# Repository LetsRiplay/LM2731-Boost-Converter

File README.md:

# LM2731-Boost-Converter
Boost converter using a 5V USB-C adapter

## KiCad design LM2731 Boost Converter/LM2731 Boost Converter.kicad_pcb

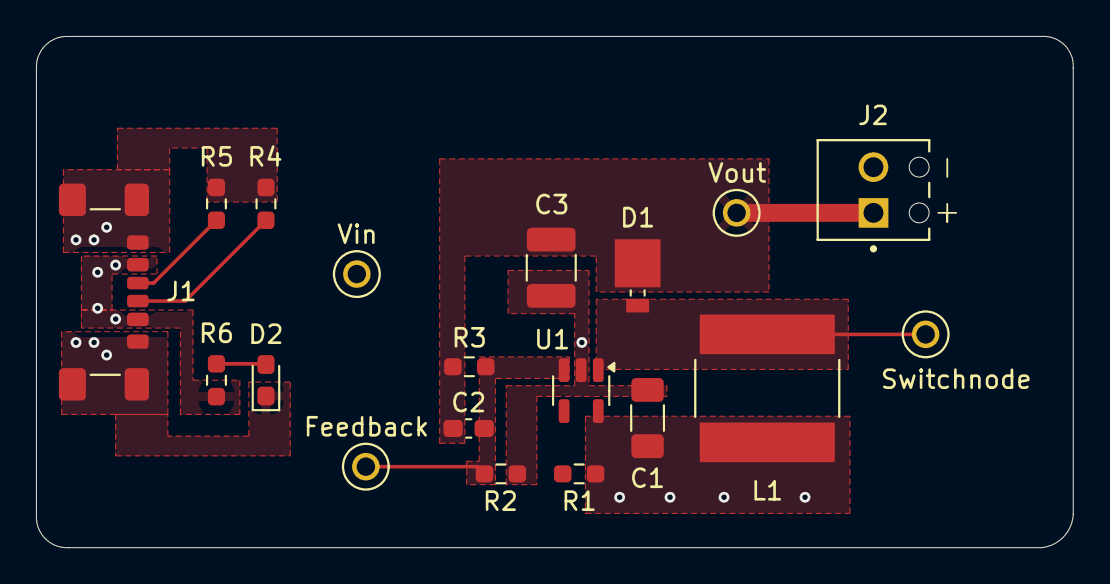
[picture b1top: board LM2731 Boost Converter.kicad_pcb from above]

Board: 4 copper layers, 57.6 x 28.4 mm, 19 parts (0 on the bottom side), 9 nets.

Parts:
C1: 2.2uF; C_1206_3216Metric_Pad1.33x1.80mm_HandSolder
C2: 240pF; C_0603_1608Metric_Pad1.08x0.95mm_HandSolder
C3: 4.7uF; C_1210_3225Metric_Pad1.33x2.70mm_HandSolder
D1: D_Schottky; D_Powermite_AK
D2: LED; LED_0603_1608Metric_Pad1.05x0.95mm_HandSolder
Feedback: TestPoint; KEYSTONE_5000
J1: USB_C_Receptacle_PowerOnly_6P; USB_C_Receptacle_GCT_USB4135-GF-A_6P_TopMnt_Horizontal
J2: Screw_Terminal_01x02; PHOENIX_1725656
L1: 43uH; IND_ASPI-8040S-430M-T
R1: 47k; R_0603_1608Metric_Pad0.98x0.95mm_HandSolder
R2: 13.3k; R_0603_1608Metric_Pad0.98x0.95mm_HandSolder
R3: 117k; R_0603_1608Metric_Pad0.98x0.95mm_HandSolder
R4, R5: 5.1k; R_0603_1608Metric_Pad0.98x0.95mm_HandSolder
R6: 70; R_0603_1608Metric_Pad0.98x0.95mm_HandSolder
Switchnode: TestPoint; KEYSTONE_5000
U1: LM2731YMF; SOT-23-5
Vin: Vin; KEYSTONE_5000
Vout: TestPoint; KEYSTONE_5000

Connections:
/Feedback: C2.2, Feedback.TP, R2.1, R3.1, U1.3 (FB)
/SwitchNode: D1.2 (A), L1.2, Switchnode.TP, U1.1 (SW)
/Vin: C1.1, J1.A9 (VBUS), J1.B9 (VBUS), L1.1, R1.1, R6.2, U1.5 (VIN), Vin.TP
/Vout: C2.1, C3.1, D1.1 (K), J2.1, R3.2, Vout.TP
GND: C1.2, C3.2, D2.1 (K), J1.A12 (GND), J1.B12 (GND), J1.S1 (SHIELD), J2.2, R2.2, R4.2, R5.2, U1.2 (GND)
unnamed: D2.2 (A), R6.1
unnamed: J1.A5 (CC1), R5.1
unnamed: J1.B5 (CC2), R4.1
unnamed: R1.2, U1.4 (EN)

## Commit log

2025-07-06 Created the main design and started sourcing parts. Also found some references for the usb pinout.
2025-07-11 Finished sourcing parts and assigning footprints. Had to add the footprint for the inductor.
2025-07-17 Started the PCB layout. Updated the Keystone 5000 test point to reflect the
    correct part.
2025-07-19 Laid out parts and added a output screw terminal.
2025-07-24 Started routing and placing planes on the PCB.
2025-07-26 Finished board layout.
